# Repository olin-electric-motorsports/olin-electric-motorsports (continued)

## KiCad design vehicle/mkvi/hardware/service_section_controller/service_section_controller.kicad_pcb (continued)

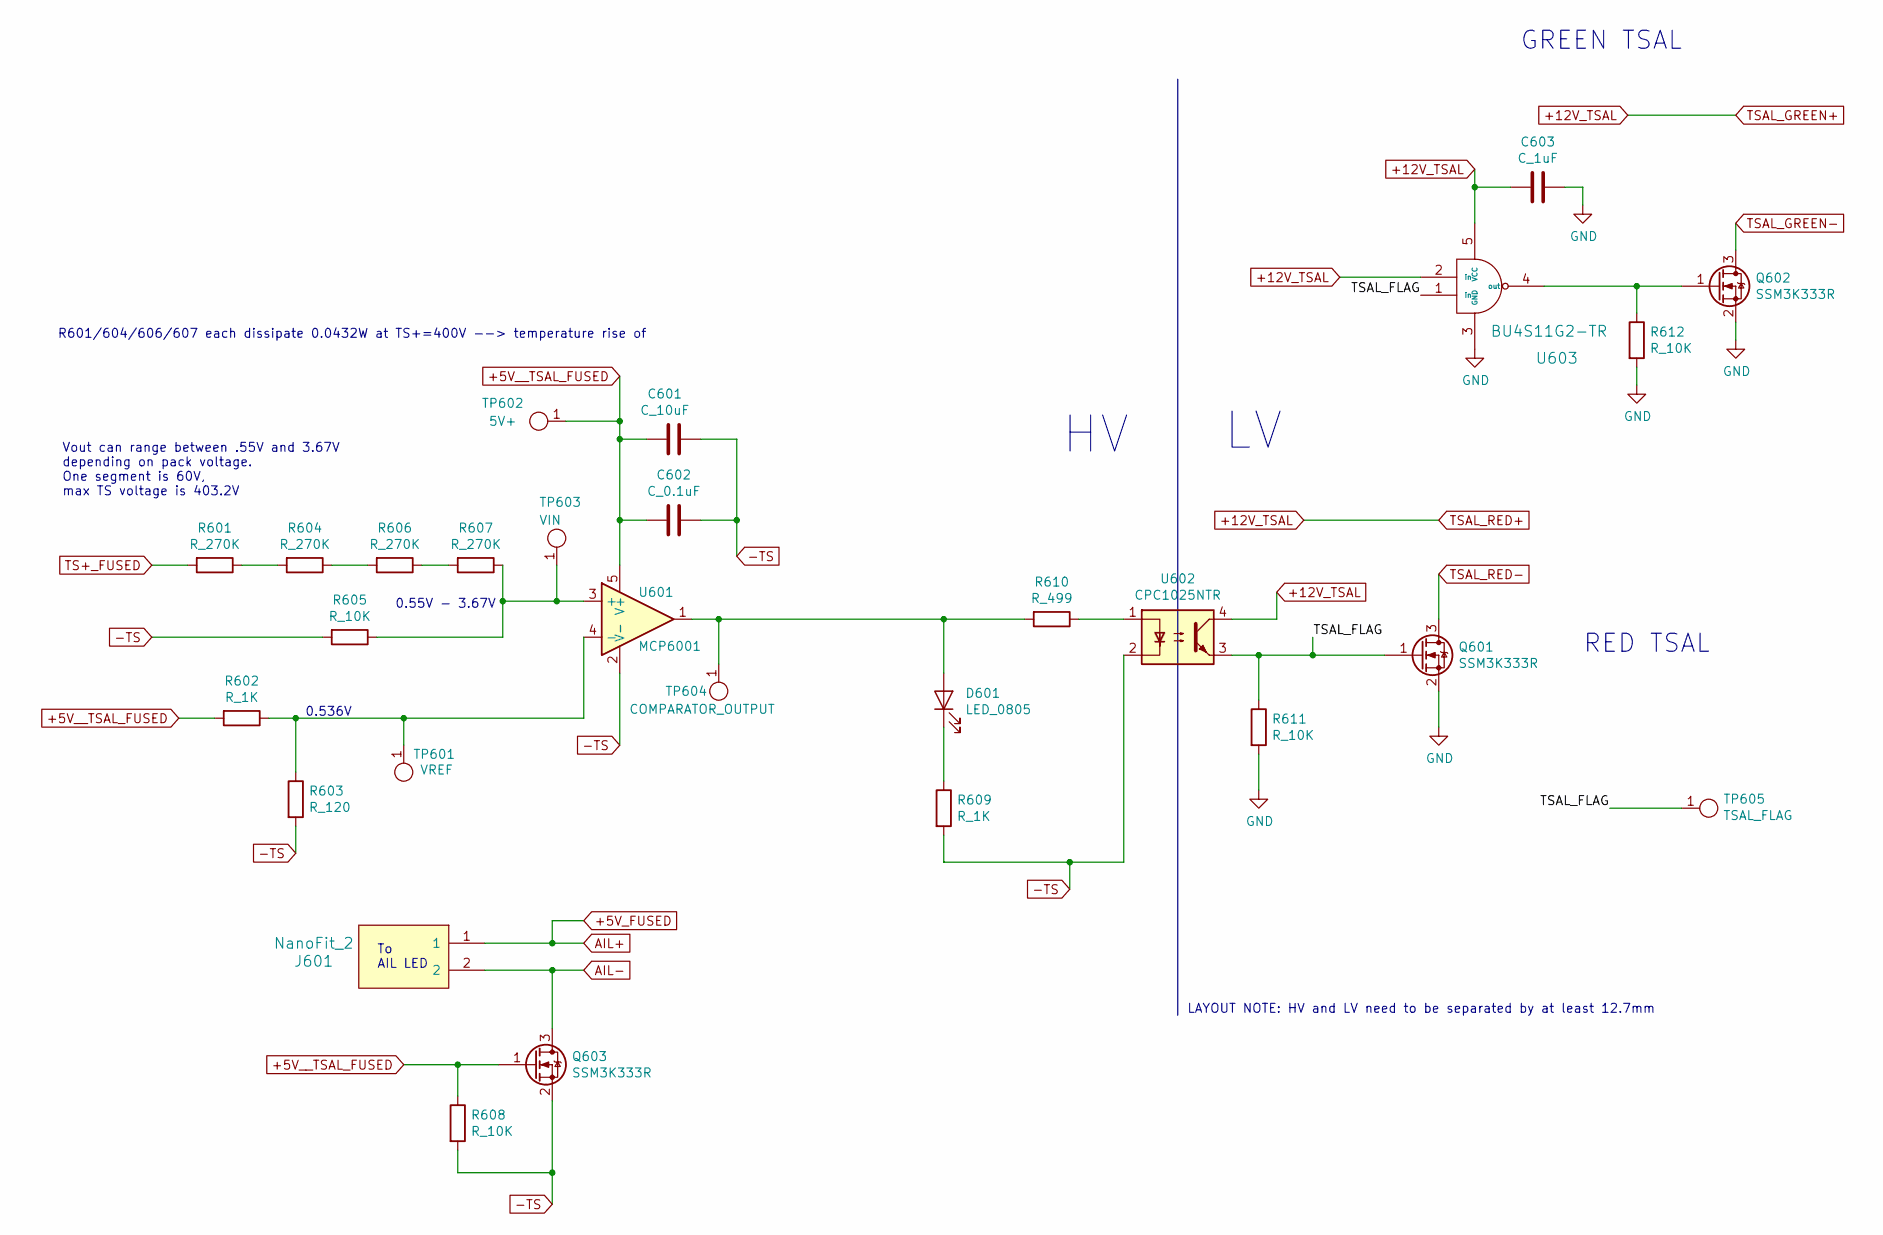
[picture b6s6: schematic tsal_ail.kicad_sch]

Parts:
C601: C_10uF; C_0805_OEM; MPN 1276-1052-1-ND
C602: C_0.1uF; C_0805_OEM; MPN 478-3352-1-ND
C603: C_1uF; C_0805_OEM
D601: LED_0805; LED_0805_OEM; MPN 475-1410-1-ND
J601: NanoFit_2; NanoFit_Molex_1x02x2.50mm_Angled_OEM; MPN WM14972-ND
Q601, Q602, Q603: SSM3K333R; SOT-23F; MPN SSM3K333RLFCT-ND
R601, R604, R606, R607: R_270K; R_0805_OEM; MPN P270KDACT-ND
R602, R609: R_1K; R_0805_OEM; MPN RNCP0805FTD1K00CT-ND
R603: R_120; R_0805_OEM; MPN 667-ERJ-6ENF1200V
R605, R608, R611, R612: R_10K; R_0805_OEM; MPN CRS0805-FX-1002ELFCT-ND
R610: R_499; R_0805_OEM; MPN P499CCT-ND
TP601: VREF; TestPoint_Pad_D1.0mm
TP602: 5V+; TestPoint_Pad_D1.0mm
TP603: VIN; TestPoint_Pad_D1.0mm
TP604: COMPARATOR_OUTPUT; TestPoint_Pad_D1.0mm
TP605: TSAL_FLAG; TestPoint_Pad_D1.0mm
U601: MCP6001; SOT-23-5; MPN MCP6001T-I/OTCT-ND
U602: CPC1025NTR; 4-pin_SOP
U603: BU4S11G2-TR; SSOP5; MPN BU4S11G2-TR

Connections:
+5V_FUSED: J601.1; also elsewhere on the board
+5V__TSAL_FUSED: C601.2, C602.2, Q603.1 (G), R602.2, R608.1, TP602.1, U601.5 (V+); also elsewhere on the board
+12V_TSAL: C603.2, U602.4, U603.2 (in), U603.5 (VCC); also elsewhere on the board
+AIR_COIL_-: C603.1, Q601.2 (S), Q602.2 (S), R611.2, R612.2, U603.3 (GND); also elsewhere on the board
-TS: C601.1, C602.1, Q603.2 (S), R603.2, R605.2, R608.2, R609.2, U601.2 (V-), U602.2; also elsewhere on the board
/tsal_ail/TSAL_FLAG: Q601.1 (G), R611.1, TP605.1, U602.3, U603.1 (in)
AIL-: J601.2, Q603.3 (D)
unnamed: D601.1 (K), R609.1
unnamed: D601.2 (A), R610.2, TP604.1, U601.1
unnamed: Q602.1 (G), R612.1, U603.4 (out)
unnamed: R601.1, R604.2
unnamed: R602.1, R603.1, TP601.1, U601.4 (-)
unnamed: R604.1, R606.2
unnamed: R605.1, R607.1, TP603.1, U601.3 (+)
unnamed: R606.1, R607.2
unnamed: R610.1, U602.1
TS+_FUSED: R601.2; also elsewhere on the board
TSAL_GREEN-: Q602.3 (D); also elsewhere on the board
TSAL_RED-: Q601.3 (D); also elsewhere on the board

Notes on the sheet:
RED TSAL
Vout can range between .55V and 3.67V depending on pack voltage. One segment is 60V, max TS voltage is 403.2V
R601/604/606/607 each dissipate 0.0432W at TS+=400V --> temperature rise of
LAYOUT NOTE: HV and LV need to be separated by at least 12.7mm
0.536V
GREEN TSAL
To AIL LED
0.55V - 3.67V

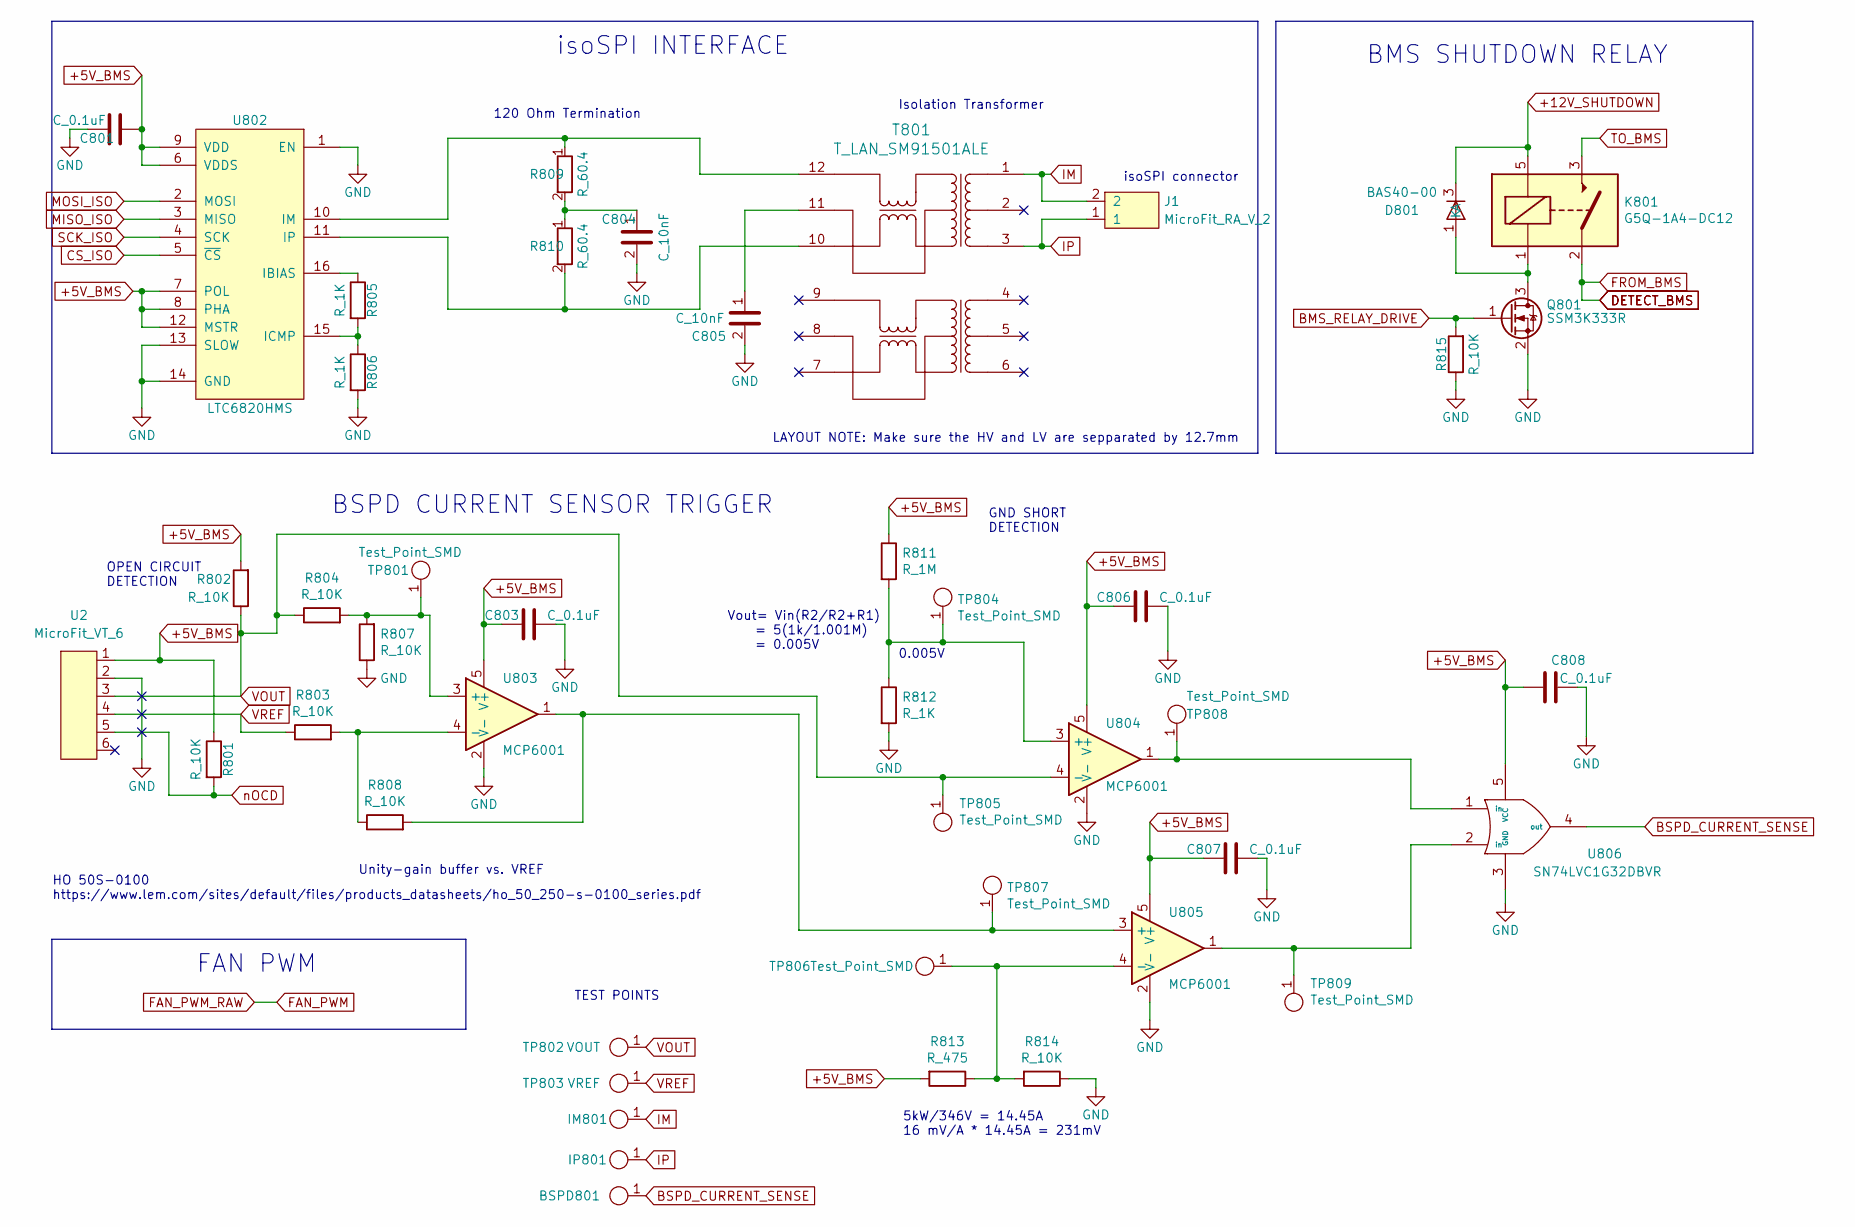
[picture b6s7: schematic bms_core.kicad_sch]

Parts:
BSPD801: Test_Point_SMD; TestPoint_Pad_D1.0mm
C801, C803, C806, C807, C808: C_0.1uF; C_0805_OEM; MPN 478-3352-1-ND
C804, C805: C_10nF; C_0805_OEM; MPN 1276-1015-1-ND
D801: BAS40-00; SOT-23; MPN 1727-4234-1-ND
IM801: Test_Point_SMD; TestPoint_Pad_D1.0mm
IP801: Test_Point_SMD; TestPoint_Pad_D1.0mm
J1: MicroFit_RA_V_2; MPN WM1865-ND
K801: G5Q-1A4-DC12; Relay_SPST_OMRON-G5Q-1A4_OEM
Q801: SSM3K333R; SOT-23F; MPN SSM3K333RLFCT-ND
R801, R802, R803, R804, R807, R808, R814, R815: R_10K; R_0805_OEM; MPN CRS0805-FX-1002ELFCT-ND
R805: R_1K; R_0805_OEM; MPN 311-3.01KCRCT-ND
R806, R812: R_1K; R_0805_OEM; MPN RNCP0805FTD1K00CT-ND
R809, R810: R_60.4; R_0805_OEM; MPN P60.4DACT-ND
R811: R_1M; R_0805_OEM; MPN RMCF0805JT1M00CT-ND
R813: R_475; R_0805_OEM; MPN 311-475CRCT-ND
T801: T_LAN_SM91501ALE; MPN SM91501ALE
TP801, TP804, TP805, TP806, TP807, TP808, TP809: Test_Point_SMD; TestPoint_Pad_D1.0mm
TP802: VOUT; TestPoint_Pad_D1.0mm
TP803: VREF; TestPoint_Pad_D1.0mm
U2: MicroFit_VT_6; MPN 430450614
U802: LTC6820HMS; MSOP-16_3x4mm_P0.5mm; MPN LTC6820HMS#TRPBFCT-ND
U803, U804, U805: MCP6001; SOT-23-5_OEM; MPN MCP6001T-I/OTCT-ND
U806: SN74LVC1G32DBVR; SOT-23-5_OEM; MPN 296-9847-1-ND

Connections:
+5V_BMS: C801.1, C803.1, C806.1, C807.1, C808.1, R801.1, R802.2, R811.1, R813.2, U2.1, U802.6 (VDDS), U802.7 (POL), U802.8 (PHA), U802.9 (VDD), U802.12 (MSTR), U803.5 (V+), U804.5 (V+), U805.5 (V+), U806.5 (VCC); also elsewhere on the board
+12V_SHUTDOWN: D801.3 (K), K801.5; also elsewhere on the board
+AIR_COIL_-: C801.2, C803.2, C804.2, C805.2, C806.2, C807.2, C808.2, Q801.2 (S), R806.2, R807.1, R812.2, R814.1, R815.1, U2.2, U802.1 (EN), U802.13 (SLOW), U802.14 (GND), U803.2 (V-), U804.2 (V-), U805.2 (V-), U806.3 (GND); also elsewhere on the board
BMS_RELAY_DRIVE: Q801.1 (G), R815.2; also elsewhere on the board
BSPD_CURRENT_SENSE: BSPD801.1, U806.4 (out); also elsewhere on the board
CS_ISO: U802.5 (~CS); also elsewhere on the board
DETECT_BMS: K801.2; also elsewhere on the board
IM: IM801.1, J1.2, T801.1
IP: IP801.1, J1.1, T801.3
MISO_ISO: U802.3 (MISO); also elsewhere on the board
MOSI_ISO: U802.2 (MOSI); also elsewhere on the board
unnamed: C804.1, R809.2, R810.1
unnamed: C805.1, T801.11
unnamed: D801.1 (A), K801.1, Q801.3 (D)
unnamed: R803.2, R808.1, U803.4 (-)
unnamed: R804.2, R807.2, TP801.1, U803.3 (+)
unnamed: R805.1, U802.16 (IBIAS)
unnamed: R805.2, R806.1, U802.15 (ICMP)
unnamed: R808.2, TP807.1, U803.1, U805.3 (+)
unnamed: R809.1, T801.12, U802.10 (IM)
unnamed: R810.2, T801.10, U802.11 (IP)
unnamed: R811.2, R812.1, TP804.1, U804.3 (+)
unnamed: R813.1, R814.2, TP806.1, U805.4 (-)
unnamed: TP808.1, U804.1, U806.1 (in)
unnamed: TP809.1, U805.1, U806.2 (in)
SCK_ISO: U802.4 (SCK); also elsewhere on the board
VOUT: R802.1, R804.1, TP802.1, TP805.1, U2.3, U804.4 (-); also elsewhere on the board
VREF: R803.1, TP803.1, U2.4; also elsewhere on the board
nOCD: R801.2, U2.5; also elsewhere on the board

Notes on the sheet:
Unity-gain buffer vs. VREF
TEST POINTS
HO 50S-0100 https://www.lem.com/sites/default/files/products_datasheets/ho_50_250-s-0100_series.pdf
isoSPI connector
isoSPI INTERFACE
Vout= Vin(R2/R2+R1) = 5(1k/1.001M) = 0.005V
Isolation Transformer
0.005V
5kW/346V = 14.45A 16 mV/A * 14.45A = 231mV
GND SHORT DETECTION
120 Ohm Termination
OPEN CIRCUIT DETECTION
FAN PWM
BMS SHUTDOWN RELAY
BSPD CURRENT SENSOR TRIGGER
LAYOUT NOTE: Make sure the HV and LV are sepparated by 12.7mm

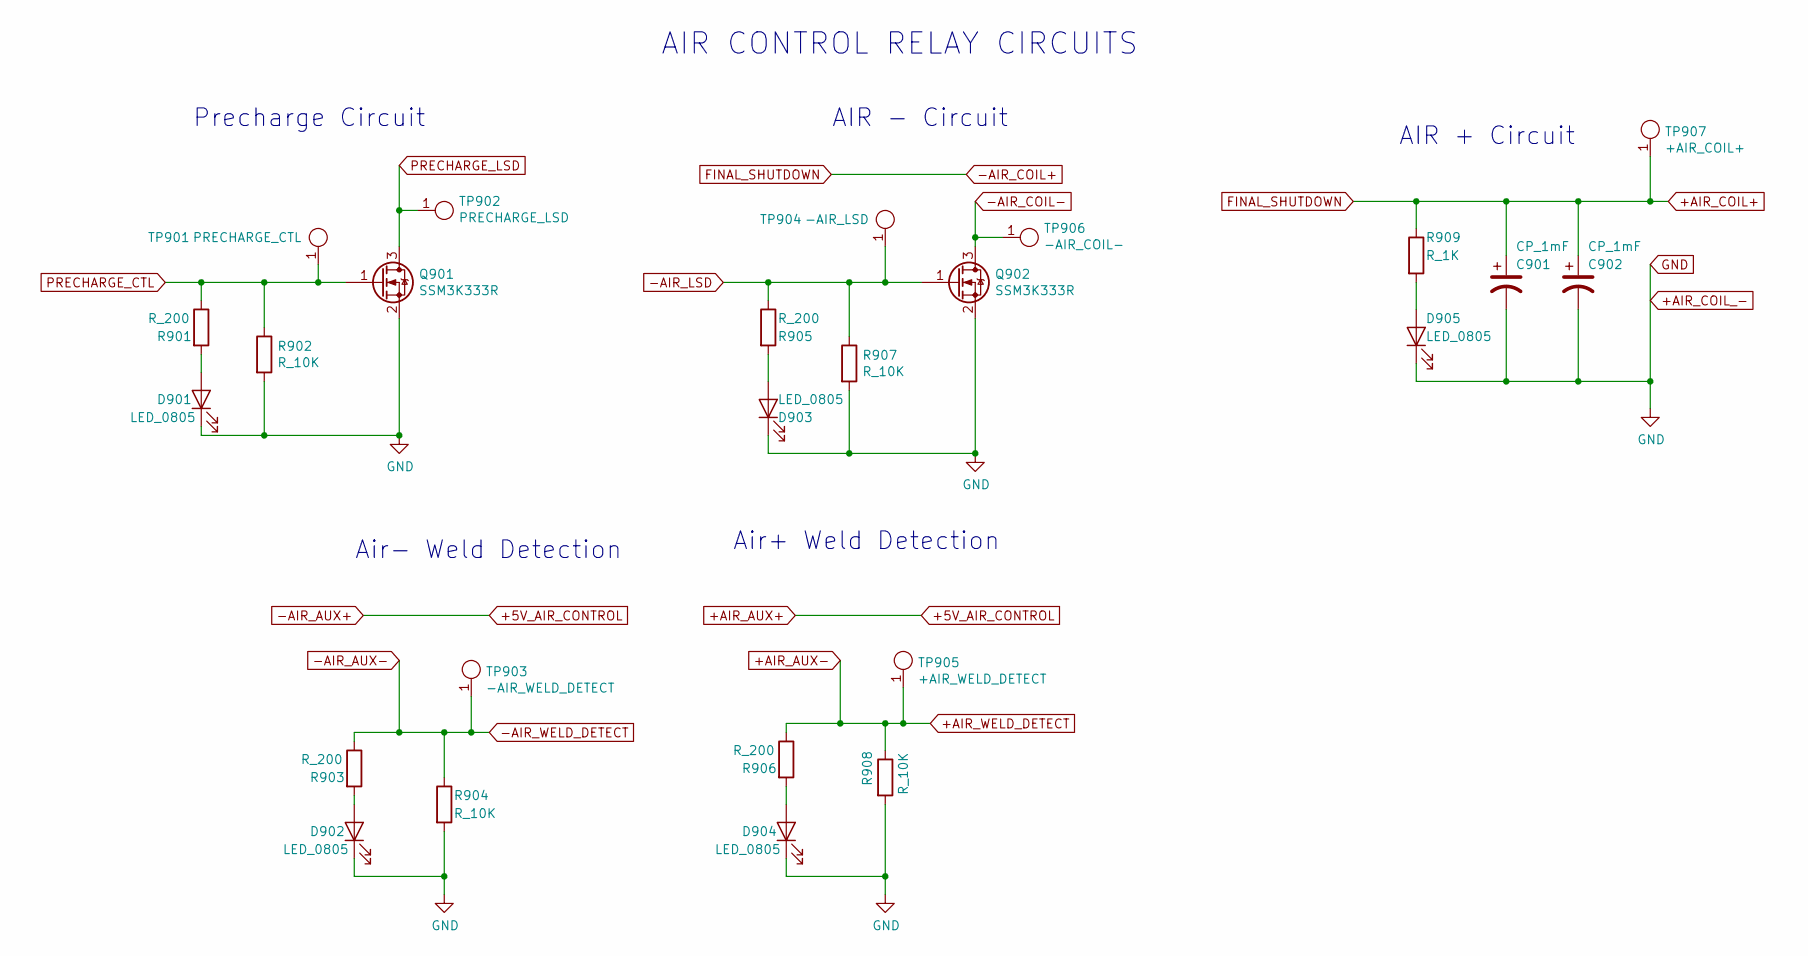
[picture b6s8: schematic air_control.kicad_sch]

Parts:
C901, C902: CP_1mF; C_Radial_D10_L13_P5_OEM; MPN 493-1305-ND
D901, D902, D903, D904, D905: LED_0805; LED_0805_OEM; MPN 475-1410-1-ND
Q901, Q902: SSM3K333R; SOT-23F; MPN SSM3K333RLFCT-ND
R901, R903, R905, R906: R_200; R_0805_OEM; MPN RMCF0805JT200RCT-ND
R902, R904, R907, R908: R_10K; R_0805_OEM; MPN CRS0805-FX-1002ELFCT-ND
R909: R_1K; R_0805_OEM; MPN RNCP0805FTD1K00CT-ND
TP901: PRECHARGE_CTL; TestPoint_Pad_D1.0mm
TP902: PRECHARGE_LSD; TestPoint_Pad_D1.0mm
TP903: -AIR_WELD_DETECT; TestPoint_Pad_D1.0mm
TP904: -AIR_LSD; TestPoint_Pad_D1.0mm
TP905: +AIR_WELD_DETECT; TestPoint_Pad_D1.0mm
TP906: -AIR_COIL-; TestPoint_Pad_D1.0mm
TP907: +AIR_COIL+; TestPoint_Pad_D1.0mm

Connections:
+AIR_AUX-: R906.1, R908.1, TP905.1; also elsewhere on the board
+AIR_COIL+: C901.1, C902.1, R909.1, TP907.1; also elsewhere on the board
+AIR_COIL_-: C901.2, C902.2, D901.1 (K), D902.1 (K), D903.1 (K), D904.1 (K), D905.1 (K), Q901.2 (S), Q902.2 (S), R902.2, R904.2, R907.2, R908.2; also elsewhere on the board
-AIR_AUX-: R903.1, R904.1, TP903.1; also elsewhere on the board
-AIR_COIL-: Q902.3 (D), TP906.1; also elsewhere on the board
-AIR_LSD: Q902.1 (G), R905.1, R907.1, TP904.1; also elsewhere on the board
unnamed: D901.2 (A), R901.2
unnamed: D902.2 (A), R903.2
unnamed: D903.2 (A), R905.2
unnamed: D904.2 (A), R906.2
unnamed: D905.2 (A), R909.2
PRECHARGE_CTL: Q901.1 (G), R901.1, R902.1, TP901.1; also elsewhere on the board
PRECHARGE_LSD: Q901.3 (D), TP902.1; also elsewhere on the board

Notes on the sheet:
Precharge Circuit
Air- Weld Detection
AIR + Circuit
Air+ Weld Detection
AIR - Circuit
AIR CONTROL RELAY CIRCUITS

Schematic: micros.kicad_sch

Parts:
C1001, C1003, C1004, C1007: C_0.1uF; C_0805_OEM; MPN 478-3352-1-ND
C1002: C_100pF; C_0805_OEM; MPN 399-1122-1-ND
C1005, C1006, C1009, C1010: C_30pF; C_0805_OEM; MPN 1276-1130-1-ND
C1008: C_100pF; C_0805_OEM; MPN 732-7852-1-ND
J1001, J1002, J1003: CONN_02X03; Pin_Header_Straight_2x03; MPN 609-3234-ND
PD1001, PD1002, PD1003, PD1004: LED_0805; LED_0805_OEM; MPN 475-1410-1-ND
R1001, R1011: R_100; R_0805_OEM; MPN RNCP0805FTD100RCT-ND
R1002, R1003: R_120_DNP; R_0805_OEM; MPN 667-ERJ-6ENF1200V
R1006, R1014: R_10K; R_0805_OEM; MPN CRS0805-FX-1002ELFCT-ND
R1007, R1008, R1009, R1010: R_200; R_0805_OEM; MPN RMCF0805JT200RCT-ND
TP1001: CAN_L; TestPoint_Pad_D2.0mm
TP1002: CANH; TestPoint_Pad_D2.0mm
U1001, U1002: MCP2561-E_SN; SOIC-8_3.9x4.9mm_Pitch1.27mm_OEM; MPN MCP2561-E/SN-ND
U1003: ATMEGA64M1; TQFP-32_7x7mm_Pitch0.8mm; MPN ATMEGA16M1-AU-ND
U1004: ATMEGA16M1; TQFP-32_7x7mm_Pitch0.8mm; MPN ATMEGA16M1-AU-ND
Y1001: Crystal_SMD; Crystal_SMD_FA238; MPN SER3686CT-ND
Y1002: Crystal_SMD; Crystal_SMD_FA238; MPN 887-1125-1-ND

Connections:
+5V_BMS: C1001.1, C1003.1, J1001.2, J1003.2, R1001.1, R1006.1, U1001.3 (VDD), U1003.4 (VCC); also elsewhere on the board
+AIR_AUX-: U1004.17 ((PCINT12/ADC8/ACMPN3/AMP1-)PC4); also elsewhere on the board
+AIR_COIL_-: C1001.2, C1002.2, C1003.2, C1004.2, C1005.2, C1006.2, C1007.2, C1008.2, C1009.2, C1010.2, J1001.6, J1002.6, J1003.6, R1007.2, R1008.2, R1009.2, R1010.2, U1001.2 (VSS), U1001.8 (STBY), U1002.2 (VSS), U1002.8 (STBY), U1003.5 (GND), U1003.20 (AGND), U1004.5 (GND), U1004.20 (AGND), Y1001.2, Y1001.4, Y1002.2, Y1002.4; also elsewhere on the board
-AIR_AUX-: U1004.18 ((PCINT13/ADC9/ACMP3/AMP1+)PC5); also elsewhere on the board
-AIR_LSD: U1004.22 ((PCINT14/ADC10/ACMP1)PC6); also elsewhere on the board
/micros/PM_DBG_1: PD1001.2 (A), U1003.14 ((PCINT22/ADC3/INT0/ACMPN2)PD6)
/micros/PM_DBG_2: PD1002.2 (A), U1003.15 ((PCINT23/ACMP0)PD7)
/micros/PM_RXCAN: U1001.4 (RXD), U1003.7 ((PCINT11/T1/ICP1B/RXCAN)PC3)
/micros/PM_TXCAN: U1001.1 (TXD), U1003.6 ((PCINT10/T0/TXCAN)PC2)
/micros/SM_DBG_1: PD1003.2 (A), U1004.14 ((PCINT22/ADC3/INT0/ACMPN2)PD6)
/micros/SM_DBG_2: PD1004.2 (A), U1004.15 ((PCINT23/ACMP0)PD7)
/micros/SM_RXCAN: U1002.4 (RXD), U1004.7 ((PCINT11/T1/ICP1B/RXCAN)PC3)
/micros/SM_TXCAN: U1002.1 (TXD), U1004.6 ((PCINT10/T0/TXCAN)PC2)
BMS_RELAY_DRIVE: U1003.25 ((PCINT15/D2A/AMP2+)PC7); also elsewhere on the board
BSPD_CURRENT_SENSE: U1003.32 ((PCINT17/CLKO/PSCIN0)PD1); also elsewhere on the board
CANH: R1002.1, R1003.1, TP1002.1, U1001.7 (CANH), U1002.7 (CANH); also elsewhere on the board
CANL: R1002.2, R1003.2, TP1001.1, U1001.6 (CANL), U1002.6 (CANL); also elsewhere on the board
CHARGE_ENABLE1: U1003.29 ((PCINT16/PSCOUT0A)PD0); also elsewhere on the board
CHARGE_ENABLE2: U1003.30 ((PCINT8/INT3/PSCOUT1A)PC0); also elsewhere on the board
CS_ISO: J1003.5, U1003.27 ((PCINT6/ADC7/PSCOUT1B)PB6); also elsewhere on the board
IMD_STATUS_OUTPUT: U1004.29 ((PCINT16/PSCOUT0A)PD0); also elsewhere on the board
MISO_ISO: J1003.1, U1003.8 ((PCINT0/MISO/PSCOUT2A)PB0); also elsewhere on the board
MOSI_ISO: J1003.4, U1003.9 ((PCINT1/MOSI/PSCOUT2B)PB1); also elsewhere on the board
unnamed: C1002.1, R1001.2, U1003.19 (AVCC)
unnamed: C1005.1, U1003.11 ((PCINT26/ADC0/XTAL2)PE2), Y1001.1
unnamed: C1006.1, U1003.10 ((PCINT25/OC0B/XTAL1)PE1), Y1001.3
unnamed: C1008.1, R1011.2, U1004.19 (AVCC)
unnamed: C1009.1, U1004.11 ((PCINT26/ADC0/XTAL2)PE2), Y1002.1
unnamed: C1010.1, U1004.10 ((PCINT25/OC0B/XTAL1)PE1), Y1002.3
unnamed: PD1001.1 (K), R1007.1
unnamed: PD1002.1 (K), R1008.1
unnamed: PD1003.1 (K), R1009.1
unnamed: PD1004.1 (K), R1010.1
PM_MISO: J1001.1, U1003.1 ((PCINT18/PSCIN2/OC1A/MISO_A)PD2)
PM_MOSI: J1001.4, U1003.2 ((PCINT19/TXD/TXLIN/OC0A/~SS/MOSI_A)PD3)
PM_RESET: J1001.5, R1006.2, U1003.31 ((PCINT24/OCD/~RESET)PE0)
PM_SCK: J1001.3, U1003.12 ((PCINT20/ADC1/RXD/RXLIN/ICP1A/SCK_A)PD4)
PRECHARGE_CTL: U1004.16 ((PCINT2/ADC5/INT1/ACMPN0)PB2); also elsewhere on the board
SCK_ISO: J1003.3, U1003.28 ((PCINT7/ADC4/SCK/PSCOUT0B)PB7); also elsewhere on the board
SM_MISO: J1002.1, U1004.1 ((PCINT18/PSCIN2/OC1A/MISO_A)PD2)
SM_MOSI: J1002.4, U1004.2 ((PCINT19/TXD/TXLIN/OC0A/~SS/MOSI_A)PD3)
SM_RESET: J1002.5, R1014.2, U1004.31 ((PCINT24/OCD/~RESET)PE0)
SM_SCK: J1002.3, U1004.12 ((PCINT20/ADC1/RXD/RXLIN/ICP1A/SCK_A)PD4)
SS_BMS: U1004.25 ((PCINT15/D2A/AMP2+)PC7); also elsewhere on the board
SS_HVD: U1004.28 ((PCINT7/ADC4/SCK/PSCOUT0B)PB7); also elsewhere on the board
SS_HVD_CONN: U1004.27 ((PCINT6/ADC7/PSCOUT1B)PB6); also elsewhere on the board
SS_IMD_LATCH: U1004.24 ((PCINT4/AMP0+)PB4); also elsewhere on the board
SS_MPC: U1004.26 ((PCINT5/ADC6/INT2/ACMPN1/AMP2-)PB5); also elsewhere on the board
SS_TSMS: U1004.23 ((PCINT3/AMP0-)PB3); also elsewhere on the board
VOUT: U1003.18 ((PCINT13/ADC9/ACMP3/AMP1+)PC5); also elsewhere on the board
VREF: U1003.17 ((PCINT12/ADC8/ACMPN3/AMP1-)PC4); also elsewhere on the board
nOCD: U1003.16 ((PCINT2/ADC5/INT1/ACMPN0)PB2); also elsewhere on the board

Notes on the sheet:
PRIMARY PROGRAMMING HEADER
atmega64m1
SECONDARY CAN TRANSCEIVER
PROGRAMMING HEADERS
atmega16m1
PROGRAMMING LEDS
PRIMARY MICRO LEDS
voltage divider on IMD schematic
SECONDARY MICRO LEDS
PRIMARY MICRO
SECONDARY PROGRAMMING HEADER
PRIMARY ISOSPI PROGRAMMING HEADER
SECONDARY MICRO
PRIMARY CAN TRANSCEIVER
CAN TRANSCEIVERS

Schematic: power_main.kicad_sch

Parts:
C1: C_2.2uF; C_0603_1608Metric; MPN 311-1451-1-ND
C2, C3: C_0.1uF; C_0805_OEM; MPN 478-3352-1-ND
COUT1: C_47uF; C_0805_OEM; MPN 587-4280-1-ND
COUT2: C_22uF; C_1206_OEM; MPN 445-11693-1-ND
COUT3: C_33uF; Fuse_1812; MPN 445-3924-1-ND
D1: D_Zener_18V; DO-214AA; MPN SMBJ5355B-TPMSCT-ND
D2, D3: LED_0805; LED_0805_OEM; MPN 475-1410-1-ND
F1, F2, F3, F4, F5, F6, F7: 500mA; Fuse_1210; MPN 507-1786-1-ND
L1: L_100uH; L_100uH_OEM; MPN 445-15759-1-ND
R1: R_1K; R_0805_OEM; MPN RNCP0805FTD1K00CT-ND
R2: R_25K; R_0805_OEM; MPN CRS0805-FX-1002ELFCT-ND
R3: R_100K; R_0805_OEM; MPN 311-54.9KCRCT-ND
R4: R_200; R_0805_OEM; MPN RMCF0805JT200RCT-ND
R5: R_0_2512; R_2512_OEM; MPN A121322CT-ND
TP1: 5V_BMS; TestPoint_Pad_D1.0mm
TP2: 5V_AIR_CONTROL; TestPoint_Pad_D1.0mm
TP3: 5V_IMD; TestPoint_Pad_D1.0mm
TP4: FB; TestPoint_Pad_D1.0mm
TP5: +Batt; TestPoint_Pad_D4.0mm
TP6: 12V_TSAL; TestPoint_Pad_D1.0mm
TP7: 12V_SHUTDOWN; TestPoint_Pad_D1.0mm
TP8: 12V_IMD; TestPoint_Pad_D1.0mm
TP9: 12V_BUCK; TestPoint_Pad_D1.0mm
TP10: BUCK_OUTPUT; TestPoint_Pad_D4.0mm
TP11: LV_GND; TestPoint_Pad_D4.0mm
U1: TPS560430YF; SOT-23-6_OEM; MPN TPS560430YFDBVR-ND

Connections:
+5V: F1.1, F2.1, R5.1; also elsewhere on the board
+5V_BMS: F1.2, TP1.1; also elsewhere on the board
+5V_IMD: F3.2, TP3.1; also elsewhere on the board
+12V_IMD: F6.2, TP8.1; also elsewhere on the board
+12V_SHUTDOWN: F5.2, TP7.1; also elsewhere on the board
+12V_TSAL: F4.2, TP6.1; also elsewhere on the board
+AIR_COIL_-: C1.2, C2.2, COUT1.2, COUT2.2, COUT3.2, D1.2 (A), D2.1 (K), D3.1 (K), R2.2, TP11.1, U1.2 (GND); also elsewhere on the board
+BATT: F4.1, F5.1, F6.1, F7.1, TP5.1; also elsewhere on the board
/power_lv/+12V_BUCK: C1.1, C2.1, D1.1 (K), F7.2, R1.1, TP9.1, U1.4 (EN), U1.5 (VIN)
unnamed: C3.1, L1.1, U1.6 (SW)
unnamed: C3.2, U1.1 (CB)
unnamed: COUT1.1, COUT2.1, COUT3.1, L1.2, R3.2, R4.1, R5.2, TP10.1
unnamed: D2.2 (A), R1.2
unnamed: D3.2 (A), R4.2
unnamed: R2.1, R3.1, TP4.1, U1.3 (FB)

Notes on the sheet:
12V Indicator
5V Indicator
Output Capacitors
OV protection
VCC jumper
FUSING TREE
Bootstrap Capacitor
Enable Pullup
Inductor
POWER FLAGS
BUCK CONVERTER
for access to ground for testing
12-16V
Input Capacitors
Feedback Divider

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
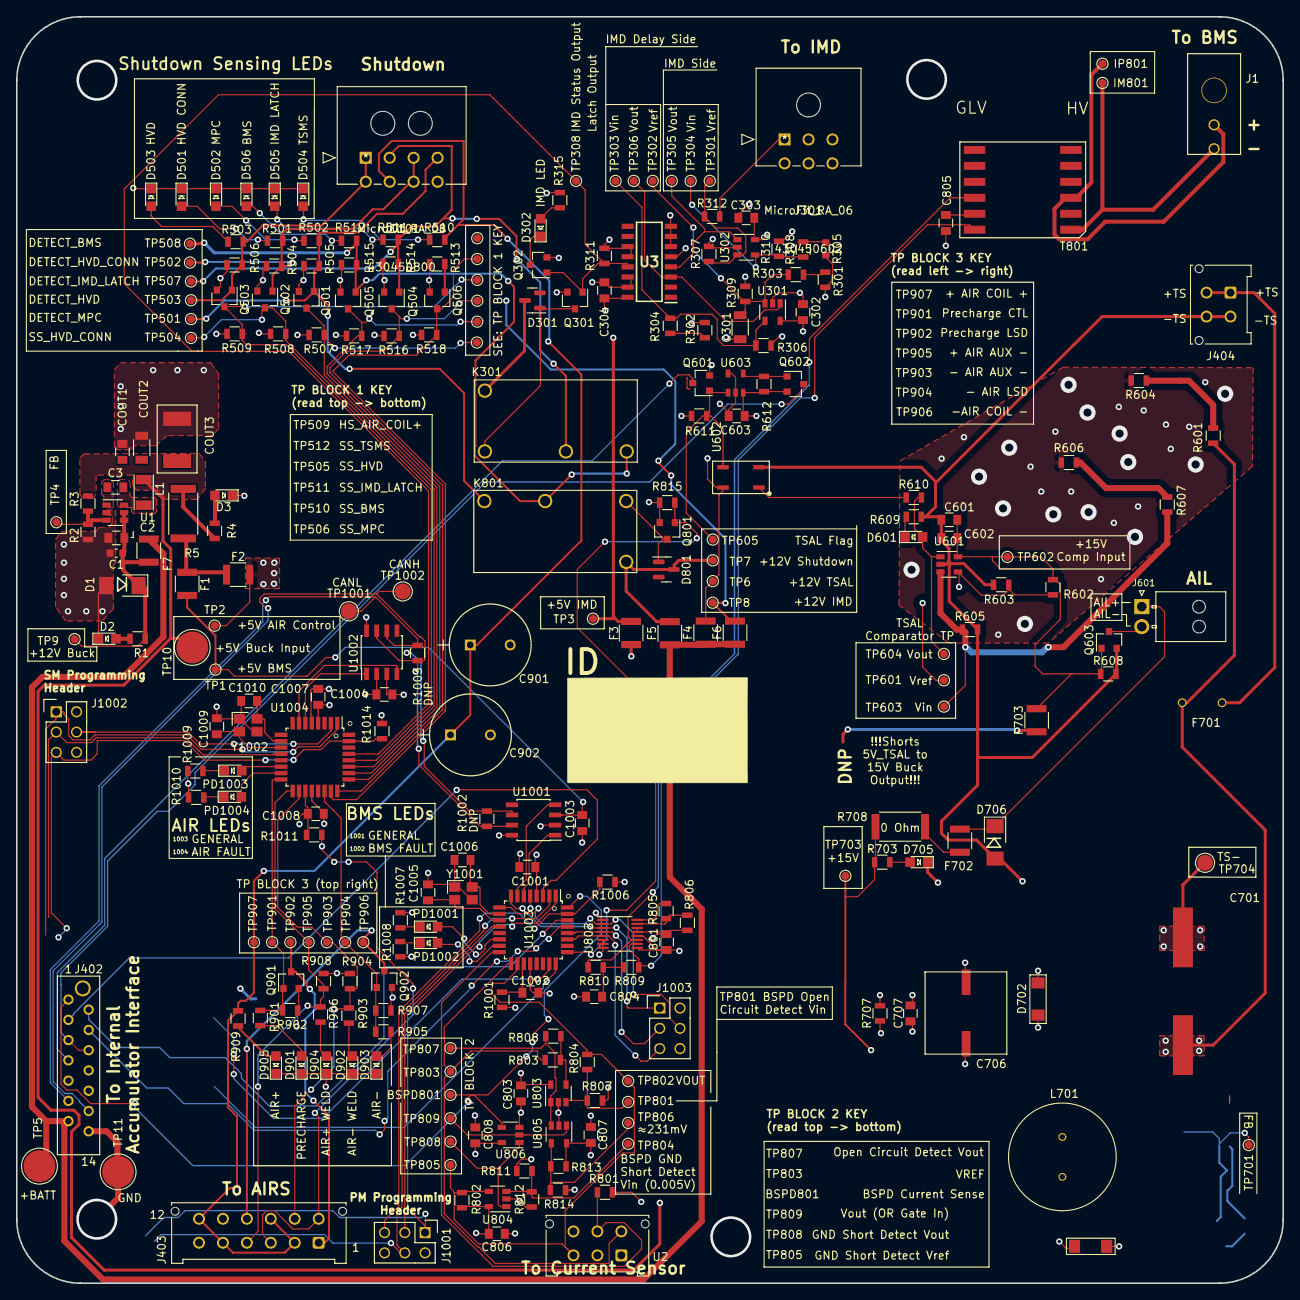
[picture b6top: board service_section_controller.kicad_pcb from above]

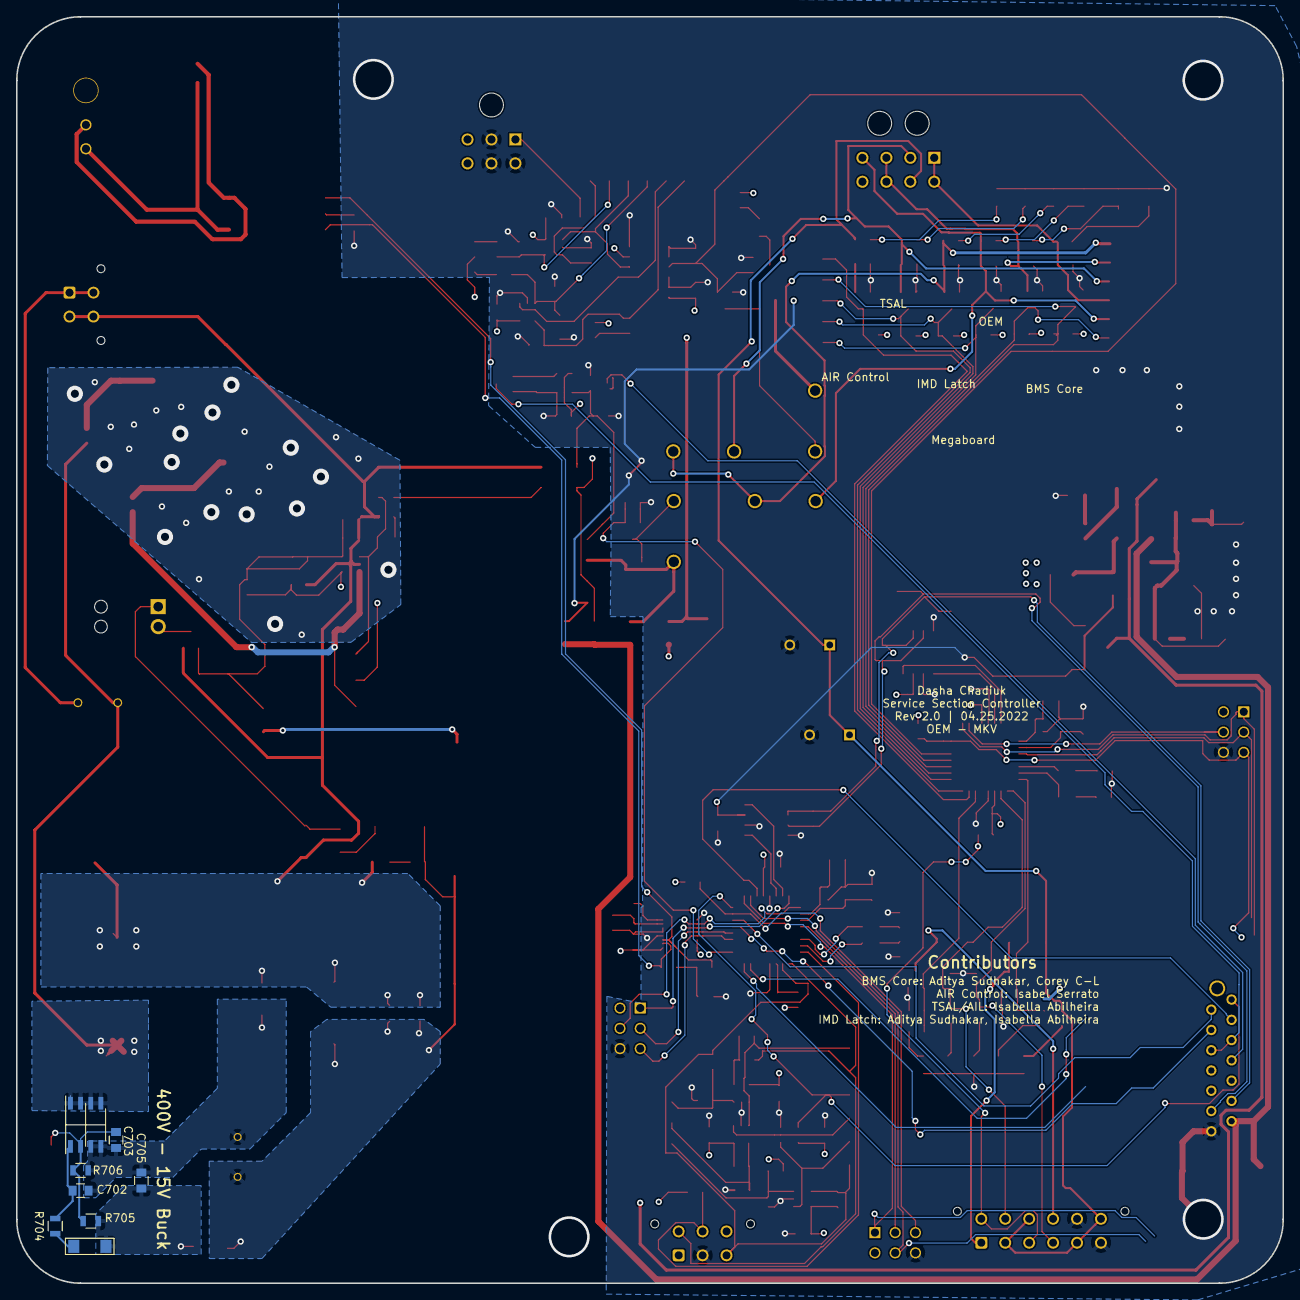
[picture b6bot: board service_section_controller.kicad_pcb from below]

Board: 4 copper layers, 158.8 x 158.8 mm, 271 parts (8 on the bottom side), 141 nets.

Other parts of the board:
J1101: MicroFit_RA_08; 430450800

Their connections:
DETECT_HVD: J1101.1, J1101.5; also elsewhere on the board
DETECT_HVD_CONN: J1101.3, J1101.7; also elsewhere on the board
DETECT_IMD_LATCH: J1101.2; also elsewhere on the board
DETECT_TSMS: J1101.6; also elsewhere on the board
